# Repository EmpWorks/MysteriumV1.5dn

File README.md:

# MysteriumV1.5dn
Hotswap,  Underglow, Encoder ,Stepped_caps

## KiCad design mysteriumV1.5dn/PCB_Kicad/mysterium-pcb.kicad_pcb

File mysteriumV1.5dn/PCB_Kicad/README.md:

# MYSTERIUM V1.5dn
Originally created by coseyfannitutti 

**TKL keyboard assembled with only through hole components, including usb type-c**

### Disclaimer
This board is a heavily-modified coseyfannitutti MYSTERIUM Pcb While the schematic, basic layout etc is essentially the same, it supports additional features like Hot-swap,Encoder etc.

Key differences:
- supports hotswap PCB sockets
- added WS2812B Led strip footprint for backlit 
- Optional encoder support
- Oled support 

Disclaimer: Use these files at your own risk.

## Assembly
For the components required, you may refer to the bill of materials here [BOM](https://octopart.com/bom-tool/wr8C8imk).

Bottom plate for the [PCB](https://github.com/TheEmperor1510/MysteriumV1.5dn/tree/main/mysteriumV1.5dn/PCB_Kicad/bottom).

need 10k 804 smd Resistor for oled 
 
All the components can be soldered using a regular soldering iron.

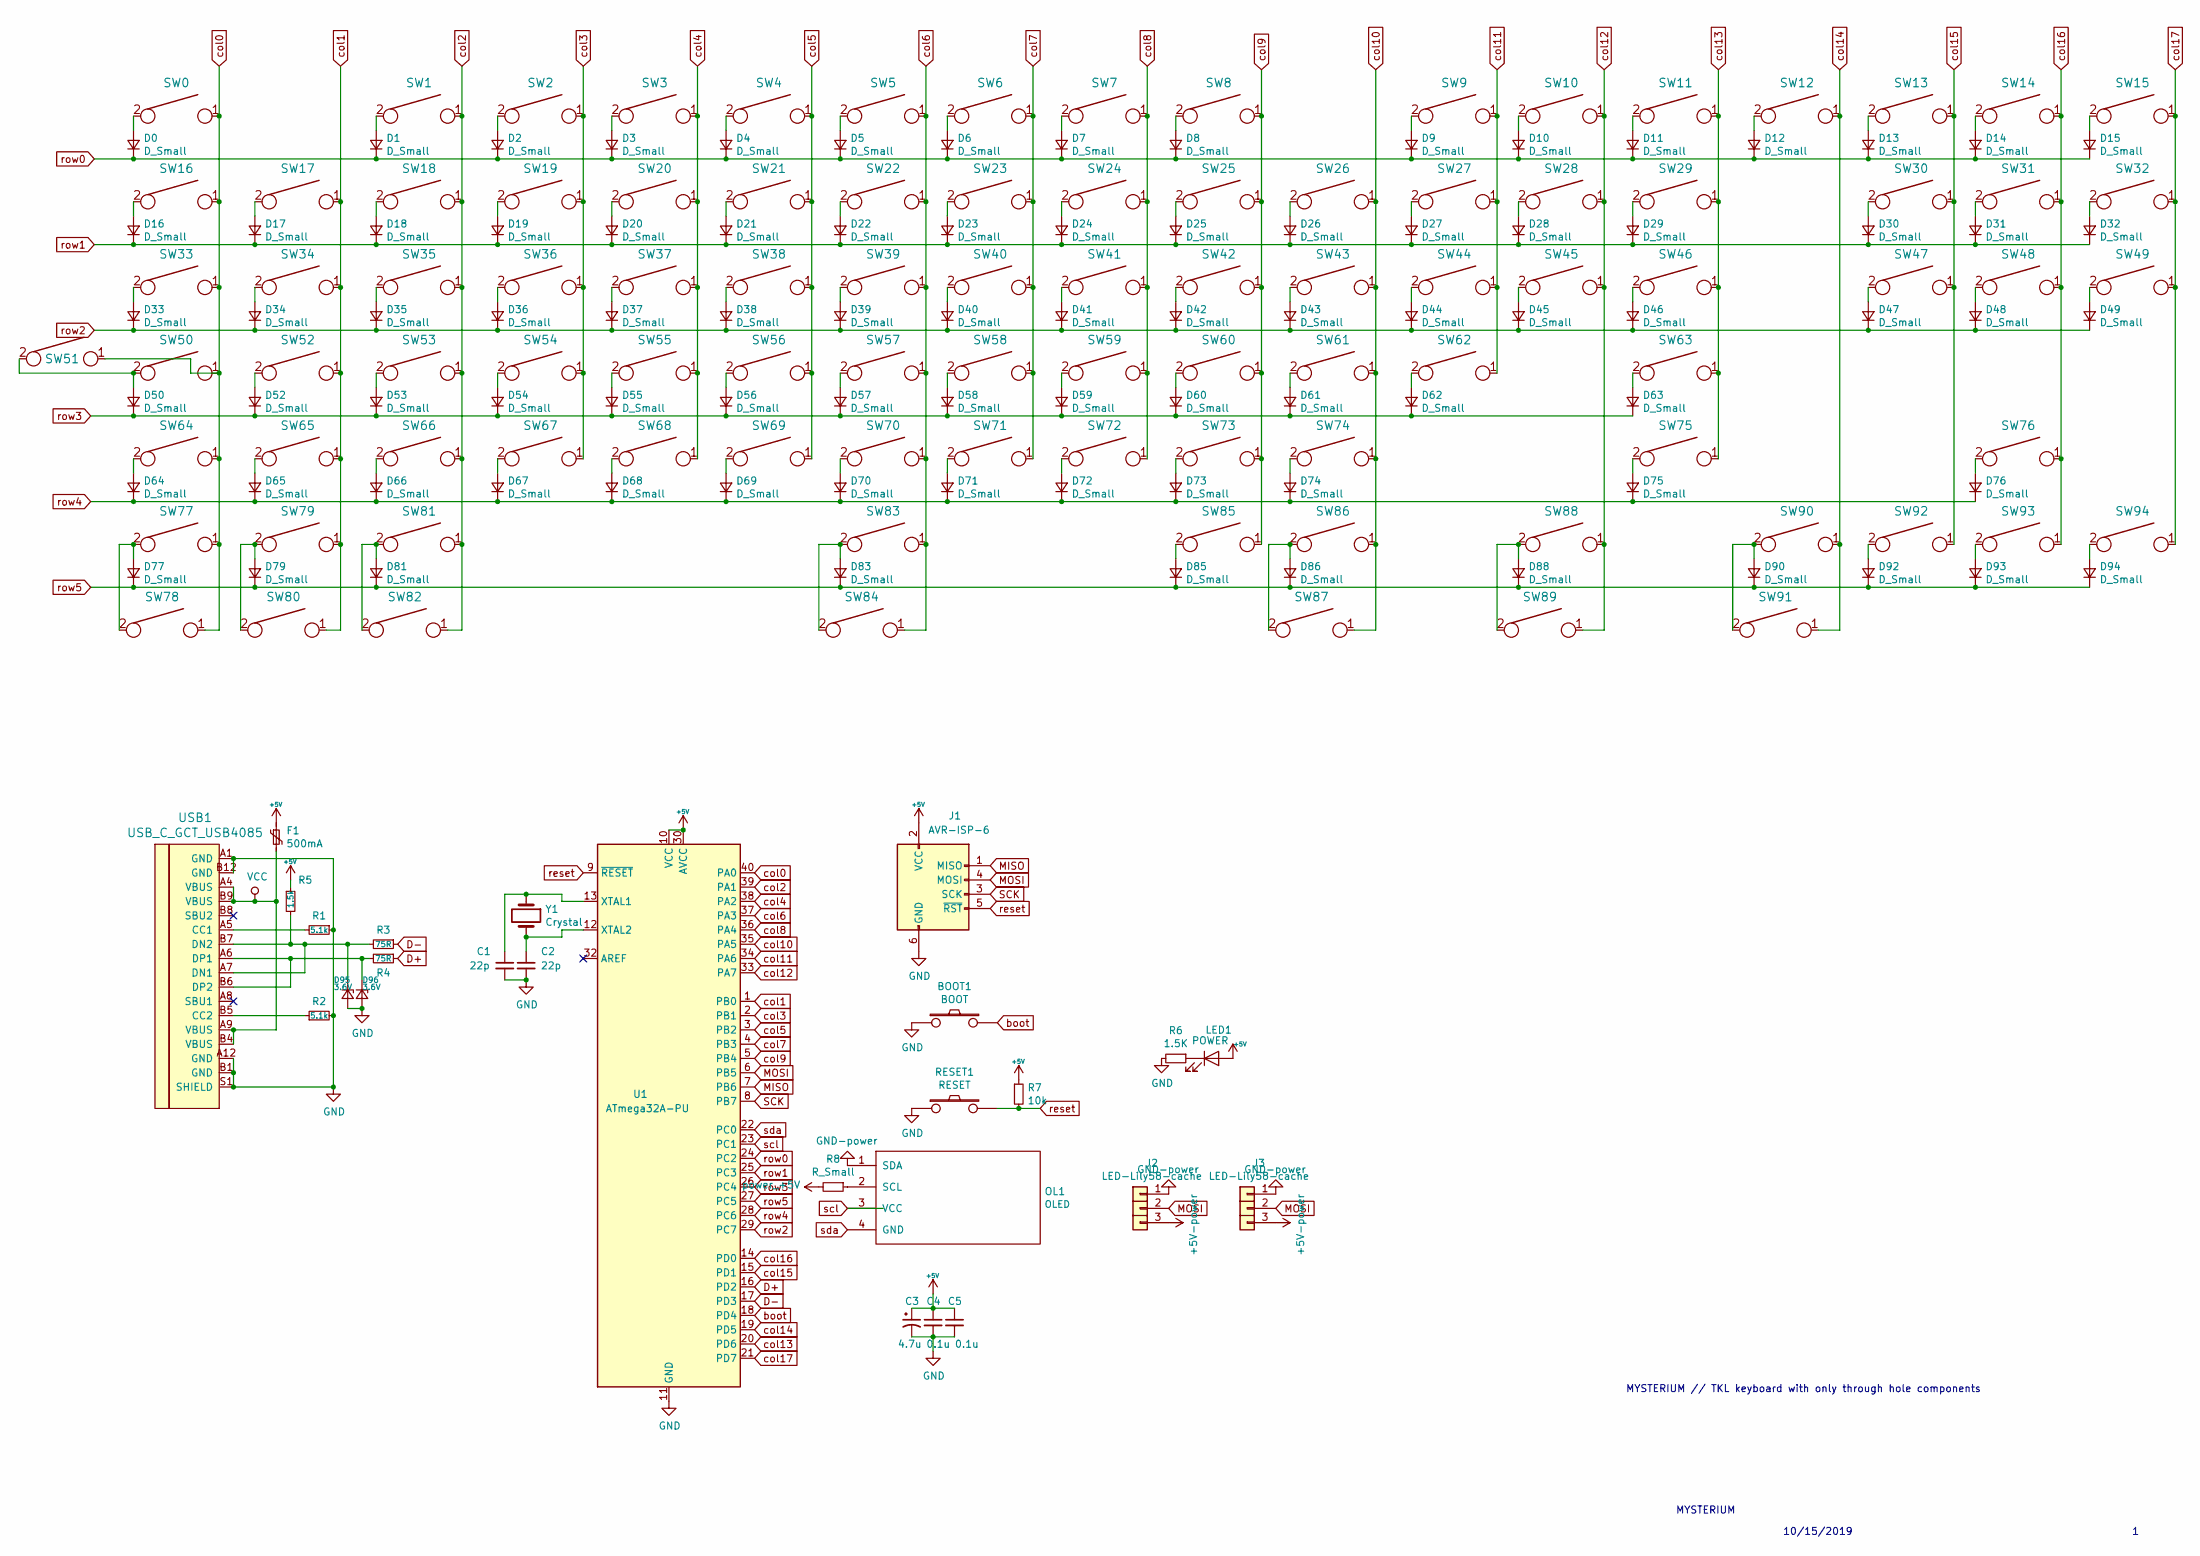
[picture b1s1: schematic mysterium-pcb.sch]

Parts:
BOOT1: BOOT; SW_PUSH_6mm
C1, C2: 22p; C_Disc_D3.0mm_W1.6mm_P2.50mm
C3: 4.7u; CP_Radial_D4.0mm_P1.50mm
C4, C5: 0.1u; C_Disc_D4.3mm_W1.9mm_P5.00mm
D0, D1, D2, D3, D4, D5, D6, D7, D8, D9, D10, D11, D12, D13, D14, D15, D16, D17, D18, D19, D20, D21, D22, D23, D24, D25, D26, D27, D28, D29, D30, D31, D32, D33, D34, D35, D36, D37, D38, D39, D40, D41, D42, D43, D44, D45, D46, D47, D48, D49, D50, D52, D53, D54, D55, D56, D57, D58, D59, D60, D61, D62, D63, D64, D65, D66, D67, D68, D69, D70, D71, D72, D73, D74, D75, D76, D77, D79, D81, D83, D85, D86, D88, D90, D92, D93, D94: D_Small; D_DO-35_SOD27_P5.08mm_Horizontal
D95, D96: 3.6V; D_DO-35_SOD27_P5.08mm_Horizontal
F1: 500mA; polyfuse_5.1mm
J1: AVR-ISP-6; AVR_ICSP_3x2
J2: LED-Lily58-cache; StripLED
J3: LED-Lily58-cache; FanPinHeader_1x03_P2.54mm_Vertical
LED1: POWER; LED_D3.0mm
OL1: OLED; PinHeader_1x04_P2.54mm_Vertical
R1, R2: 5.1k; R_Axial_DIN0204_L3.6mm_D1.6mm_P7.62mm_Horizontal
R3, R4: 75R; R_Axial_DIN0204_L3.6mm_D1.6mm_P7.62mm_Horizontal
R5: 1.5k; R_Axial_DIN0204_L3.6mm_D1.6mm_P7.62mm_Horizontal
R6: 1.5K; R_Axial_DIN0204_L3.6mm_D1.6mm_P7.62mm_Horizontal
R7: 10k; R_Axial_DIN0204_L3.6mm_D1.6mm_P7.62mm_Horizontal
R8: R_Small; R_0805_2012Metric_Pad1.20x1.40mm_HandSolder
RESET1: RESET; SW_PUSH_6mm
SW0, SW1, SW2, SW3, SW4, SW5, SW6, SW7, SW8, SW9, SW10, SW11, SW12, SW13, SW14, SW15, SW16, SW17, SW18, SW19, SW20, SW21, SW22, SW23, SW24, SW25, SW26, SW27, SW28, SW30, SW31, SW32, SW33, SW34, SW35, SW36, SW37, SW38, SW39, SW40, SW41, SW42, SW43, SW44, SW45, SW46, SW47, SW48, SW49, SW50, SW51, SW52, SW53, SW54, SW55, SW56, SW57, SW58, SW59, SW60, SW61, SW62, SW65, SW66, SW67, SW68, SW69, SW70, SW71, SW72, SW73, SW74, SW76, SW77, SW78, SW79, SW80, SW81, SW82, SW83, SW84, SW85, SW86, SW87, SW88, SW89, SW90, SW91, SW92, SW93, SW94: KEYSW; Kailh-PCB-Socket-1U-Cutout
SW29, SW63, SW64, SW75: KEYSW; Kailh-PCB-Socket-2U
U1: ATmega32A-PU; DIP-40_W15.24mm
USB1: USB_C_GCT_USB4085
Y1: Crystal; Crystal_HC49-4H_Vertical

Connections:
D+: R4.1, U1.16 (PD2)
D-: R3.1, U1.17 (PD3)
MISO: J1.1 (MISO), U1.7 (PB6)
MOSI: J1.4 (MOSI), J2.2, J3.2, U1.6 (PB5); also elsewhere on the board
unnamed: C1.1, U1.13 (XTAL1), Y1.1
unnamed: C2.1, U1.12 (XTAL2), Y1.2
unnamed: D0.2 (A), SW0.2
unnamed: D1.2 (A), SW1.2
unnamed: D2.2 (A), SW2.2
unnamed: D3.2 (A), SW3.2
unnamed: D4.2 (A), SW4.2
unnamed: D5.2 (A), SW5.2
unnamed: D6.2 (A), SW6.2
unnamed: D7.2 (A), SW7.2
unnamed: D8.2 (A), SW8.2
unnamed: D9.2 (A), SW9.2
unnamed: D10.2 (A), SW10.2
unnamed: D11.2 (A), SW11.2
unnamed: D12.2 (A), SW12.2
unnamed: D13.2 (A), SW13.2
unnamed: D14.2 (A), SW14.2
unnamed: D15.2 (A), SW15.2
unnamed: D16.2 (A), SW16.2
unnamed: D17.2 (A), SW17.2
unnamed: D18.2 (A), SW18.2
unnamed: D19.2 (A), SW19.2
unnamed: D20.2 (A), SW20.2
unnamed: D21.2 (A), SW21.2
unnamed: D22.2 (A), SW22.2
unnamed: D23.2 (A), SW23.2
unnamed: D24.2 (A), SW24.2
unnamed: D25.2 (A), SW25.2
unnamed: D26.2 (A), SW26.2
unnamed: D27.2 (A), SW27.2
unnamed: D28.2 (A), SW28.2
unnamed: D29.2 (A), SW29.2
unnamed: D30.2 (A), SW30.2
unnamed: D31.2 (A), SW31.2
unnamed: D32.2 (A), SW32.2
unnamed: D33.2 (A), SW33.2
unnamed: D34.2 (A), SW34.2
unnamed: D35.2 (A), SW35.2
unnamed: D36.2 (A), SW36.2
unnamed: D37.2 (A), SW37.2
unnamed: D38.2 (A), SW38.2
unnamed: D39.2 (A), SW39.2
unnamed: D40.2 (A), SW40.2
unnamed: D41.2 (A), SW41.2
unnamed: D42.2 (A), SW42.2
unnamed: D43.2 (A), SW43.2
unnamed: D44.2 (A), SW44.2
unnamed: D45.2 (A), SW45.2
unnamed: D46.2 (A), SW46.2
unnamed: D47.2 (A), SW47.2
unnamed: D48.2 (A), SW48.2
unnamed: D49.2 (A), SW49.2
unnamed: D50.2 (A), SW50.2, SW51.2
unnamed: D52.2 (A), SW52.2
unnamed: D53.2 (A), SW53.2
unnamed: D54.2 (A), SW54.2
unnamed: D55.2 (A), SW55.2
unnamed: D56.2 (A), SW56.2
unnamed: D57.2 (A), SW57.2
unnamed: D58.2 (A), SW58.2
unnamed: D59.2 (A), SW59.2
unnamed: D60.2 (A), SW60.2
unnamed: D61.2 (A), SW61.2
unnamed: D62.2 (A), SW62.2
unnamed: D63.2 (A), SW63.2
unnamed: D64.2 (A), SW64.2
unnamed: D65.2 (A), SW65.2
unnamed: D66.2 (A), SW66.2
unnamed: D67.2 (A), SW67.2
unnamed: D68.2 (A), SW68.2
unnamed: D69.2 (A), SW69.2
unnamed: D70.2 (A), SW70.2
unnamed: D71.2 (A), SW71.2
unnamed: D72.2 (A), SW72.2
unnamed: D73.2 (A), SW73.2
unnamed: D74.2 (A), SW74.2
unnamed: D75.2 (A), SW75.2
unnamed: D76.2 (A), SW76.2
unnamed: D77.2 (A), SW77.2, SW78.2
unnamed: D79.2 (A), SW79.2, SW80.2
unnamed: D81.2 (A), SW81.2, SW82.2
unnamed: D83.2 (A), SW83.2, SW84.2
unnamed: D85.2 (A), SW85.2
unnamed: D86.2 (A), SW86.2, SW87.2
unnamed: D88.2 (A), SW88.2, SW89.2
unnamed: D90.2 (A), SW90.2, SW91.2
unnamed: D92.2 (A), SW92.2
unnamed: D93.2 (A), SW93.2
unnamed: D94.2 (A), SW94.2
unnamed: D95.1 (K), R3.2, R5.2, USB1.A7 (DN1), USB1.B7 (DN2)
unnamed: D96.1 (K), R4.2, USB1.A6 (DP1), USB1.B6 (DP2)
unnamed: LED1.1 (K), R6.1
unnamed 96: OL1.2 (SCL), R8.1; also elsewhere on the board
unnamed: R1.2, USB1.A5 (CC1)
unnamed: R2.1, USB1.B5 (CC2)
SCK: J1.3 (SCK), U1.8 (PB7)
VCC: F1.2, USB1.A4 (VBUS), USB1.A9 (VBUS), USB1.B4 (VBUS), USB1.B9 (VBUS)
boot: BOOT1.2, U1.18 (PD4)
col0: SW0.1, SW16.1, SW33.1, SW50.1, SW51.1, SW64.1, SW77.1, SW78.1, U1.40 (PA0)
col1: SW17.1, SW34.1, SW52.1, SW65.1, SW79.1, SW80.1, U1.1 (PB0)
col2: SW1.1, SW18.1, SW35.1, SW53.1, SW66.1, SW81.1, SW82.1, U1.39 (PA1)
col3: SW2.1, SW19.1, SW36.1, SW54.1, SW67.1, U1.2 (PB1)
col4: SW3.1, SW20.1, SW37.1, SW55.1, SW68.1, U1.38 (PA2)
col5: SW4.1, SW21.1, SW38.1, SW56.1, SW69.1, U1.3 (PB2)
col6: SW5.1, SW22.1, SW39.1, SW57.1, SW70.1, SW83.1, SW84.1, U1.37 (PA3)
col7: SW6.1, SW23.1, SW40.1, SW58.1, SW71.1, U1.4 (PB3)
col8: SW7.1, SW24.1, SW41.1, SW59.1, SW72.1, U1.36 (PA4)
col9: SW8.1, SW25.1, SW42.1, SW60.1, SW73.1, SW85.1, U1.5 (PB4)
col10: SW26.1, SW43.1, SW61.1, SW74.1, SW86.1, SW87.1, U1.35 (PA5)
col11: SW9.1, SW27.1, SW44.1, SW62.1, U1.34 (PA6)
col12: SW10.1, SW28.1, SW45.1, SW88.1, SW89.1, U1.33 (PA7)
col13: SW11.1, SW29.1, SW46.1, SW63.1, SW75.1, U1.20 (PD6)
col14: SW12.1, SW90.1, SW91.1, U1.19 (PD5)
col15: SW13.1, SW30.1, SW47.1, SW92.1, U1.15 (PD1)
col16: SW14.1, SW31.1, SW48.1, SW76.1, SW93.1, U1.14 (PD0)
col17: SW15.1, SW32.1, SW49.1, SW94.1, U1.21 (PD7)
reset: J1.5 (~RST), R7.2, RESET1.2, U1.9 (~RESET)
row0: D0.1 (K), D1.1 (K), D2.1 (K), D3.1 (K), D4.1 (K), D5.1 (K), D6.1 (K), D7.1 (K), D8.1 (K), D9.1 (K), D10.1 (K), D11.1 (K), D12.1 (K), D13.1 (K), D14.1 (K), D15.1 (K), U1.24 (PC2)
row1: D16.1 (K), D17.1 (K), D18.1 (K), D19.1 (K), D20.1 (K), D21.1 (K), D22.1 (K), D23.1 (K), D24.1 (K), D25.1 (K), D26.1 (K), D27.1 (K), D28.1 (K), D29.1 (K), D30.1 (K), D31.1 (K), D32.1 (K), U1.25 (PC3)
row2: D33.1 (K), D34.1 (K), D35.1 (K), D36.1 (K), D37.1 (K), D38.1 (K), D39.1 (K), D40.1 (K), D41.1 (K), D42.1 (K), D43.1 (K), D44.1 (K), D45.1 (K), D46.1 (K), D47.1 (K), D48.1 (K), D49.1 (K), U1.29 (PC7)
row3: D50.1 (K), D52.1 (K), D53.1 (K), D54.1 (K), D55.1 (K), D56.1 (K), D57.1 (K), D58.1 (K), D59.1 (K), D60.1 (K), D61.1 (K), D62.1 (K), D63.1 (K), U1.26 (PC4)
row4: D64.1 (K), D65.1 (K), D66.1 (K), D67.1 (K), D68.1 (K), D69.1 (K), D70.1 (K), D71.1 (K), D72.1 (K), D73.1 (K), D74.1 (K), D75.1 (K), D76.1 (K), U1.28 (PC6)
row5: D77.1 (K), D79.1 (K), D81.1 (K), D83.1 (K), D85.1 (K), D86.1 (K), D88.1 (K), D90.1 (K), D92.1 (K), D93.1 (K), D94.1 (K), U1.27 (PC5)
scl: OL1.3 (VCC), U1.23 (PC1)
sda: OL1.4 (GND), U1.22 (PC0)

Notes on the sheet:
MYSTERIUM // TKL keyboard with only through hole components
10/15/2019
MYSTERIUM

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
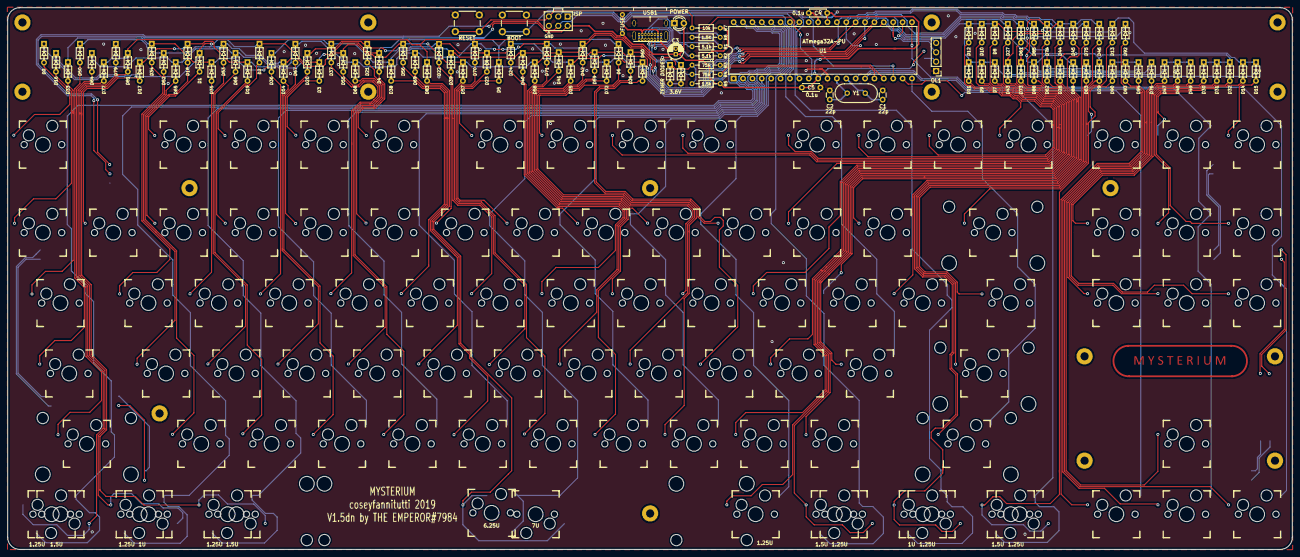
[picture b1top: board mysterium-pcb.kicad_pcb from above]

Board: 2 copper layers, 347.7 x 146.6 mm, 219 parts (1 on the bottom side), 131 nets.

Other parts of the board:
J2#2, J2#3, J2#4, J2#5, J2#6, J2#7, J2#8, J2#9, J2#10, J2#11, J2#12: LED-Lily58-cache; StripLED
R10k: R_Small; R_0805_2012Metric_Pad1.20x1.40mm_HandSolder
ST83: 6.25U; MX-6.25U-Stabilizer
ST84: 7U; MX-7U-Stabilizer

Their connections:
MOSI: J2#2.2, J2#3.2, J2#4.2, J2#5.2, J2#6.2, J2#7.2, J2#8.2, J2#9.2, J2#10.2, J2#11.2, J2#12.2; also elsewhere on the board
unnamed 96: R10k.1; also elsewhere on the board

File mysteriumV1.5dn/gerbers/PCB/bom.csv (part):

Designator,Footprint,Quantity,Value,LCSC Part #
ST83,MX-6.25U-Stabilizer,1,6.25U,
SW17,Kailh-PCB-Socket-1U-Cutout,1,KEYSW,
SW41,Kailh-PCB-Socket-1U-Cutout,1,KEYSW,
ST84,MX-7U-Stabilizer,1,7U,
C3,CP_Radial_D4.0mm_P1.50mm,1,4.7u,
LED1,LED_D3.0mm,1,POWER,
D28,D_DO-35_SOD27_P5.08mm_Horizontal,1,D_Small,
D36,D_DO-35_SOD27_P5.08mm_Horizontal,1,D_Small,
D11,D_DO-35_SOD27_P5.08mm_Horizontal,1,D_Small,
D14,D_DO-35_SOD27_P5.08mm_Horizontal,1,D_Small,
D90,D_DO-35_SOD27_P5.08mm_Horizontal,1,D_Small,
D92,D_DO-35_SOD27_P5.08mm_Horizontal,1,D_Small,
U1,DIP-40_W15.24mm,1,ATmega32A-PU,
BOOT1,SW_PUSH_6mm,1,BOOT,
C1,C_Disc_D3.0mm_W1.6mm_P2.50mm,1,22p,
C2,C_Disc_D3.0mm_W1.6mm_P2.50mm,1,22p,
C4,C_Disc_D4.3mm_W1.9mm_P5.00mm,1,0.1u,
C5,C_Disc_D4.3mm_W1.9mm_P5.00mm,1,0.1u,
D0,D_DO-35_SOD27_P5.08mm_Horizontal,1,D_Small,
D1,D_DO-35_SOD27_P5.08mm_Horizontal,1,D_Small,
D2,D_DO-35_SOD27_P5.08mm_Horizontal,1,D_Small,
D3,D_DO-35_SOD27_P5.08mm_Horizontal,1,D_Small,
D4,D_DO-35_SOD27_P5.08mm_Horizontal,1,D_Small,
D5,D_DO-35_SOD27_P5.08mm_Horizontal,1,D_Small,
D6,D_DO-35_SOD27_P5.08mm_Horizontal,1,D_Small,
D7,D_DO-35_SOD27_P5.08mm_Horizontal,1,D_Small,
D8,D_DO-35_SOD27_P5.08mm_Horizontal,1,D_Small,
D9,D_DO-35_SOD27_P5.08mm_Horizontal,1,D_Small,
D10,D_DO-35_SOD27_P5.08mm_Horizontal,1,D_Small,
D12,D_DO-35_SOD27_P5.08mm_Horizontal,1,D_Small,
D13,D_DO-35_SOD27_P5.08mm_Horizontal,1,D_Small,
D15,D_DO-35_SOD27_P5.08mm_Horizontal,1,D_Small,
D16,D_DO-35_SOD27_P5.08mm_Horizontal,1,D_Small,
D17,D_DO-35_SOD27_P5.08mm_Horizontal,1,D_Small,
D18,D_DO-35_SOD27_P5.08mm_Horizontal,1,D_Small,
D19,D_DO-35_SOD27_P5.08mm_Horizontal,1,D_Small,
D20,D_DO-35_SOD27_P5.08mm_Horizontal,1,D_Small,
D21,D_DO-35_SOD27_P5.08mm_Horizontal,1,D_Small,
D22,D_DO-35_SOD27_P5.08mm_Horizontal,1,D_Small,
D23,D_DO-35_SOD27_P5.08mm_Horizontal,1,D_Small,
D24,D_DO-35_SOD27_P5.08mm_Horizontal,1,D_Small,
D25,D_DO-35_SOD27_P5.08mm_Horizontal,1,D_Small,
D26,D_DO-35_SOD27_P5.08mm_Horizontal,1,D_Small,
D27,D_DO-35_SOD27_P5.08mm_Horizontal,1,D_Small,
D29,D_DO-35_SOD27_P5.08mm_Horizontal,1,D_Small,
D30,D_DO-35_SOD27_P5.08mm_Horizontal,1,D_Small,
D31,D_DO-35_SOD27_P5.08mm_Horizontal,1,D_Small,
D32,D_DO-35_SOD27_P5.08mm_Horizontal,1,D_Small,
D33,D_DO-35_SOD27_P5.08mm_Horizontal,1,D_Small,
D34,D_DO-35_SOD27_P5.08mm_Horizontal,1,D_Small,
D35,D_DO-35_SOD27_P5.08mm_Horizontal,1,D_Small,
D37,D_DO-35_SOD27_P5.08mm_Horizontal,1,D_Small,
D38,D_DO-35_SOD27_P5.08mm_Horizontal,1,D_Small,
D39,D_DO-35_SOD27_P5.08mm_Horizontal,1,D_Small,
D40,D_DO-35_SOD27_P5.08mm_Horizontal,1,D_Small,
D41,D_DO-35_SOD27_P5.08mm_Horizontal,1,D_Small,
D42,D_DO-35_SOD27_P5.08mm_Horizontal,1,D_Small,
D43,D_DO-35_SOD27_P5.08mm_Horizontal,1,D_Small,
D44,D_DO-35_SOD27_P5.08mm_Horizontal,1,D_Small,
D45,D_DO-35_SOD27_P5.08mm_Horizontal,1,D_Small,
D46,D_DO-35_SOD27_P5.08mm_Horizontal,1,D_Small,
D47,D_DO-35_SOD27_P5.08mm_Horizontal,1,D_Small,
D48,D_DO-35_SOD27_P5.08mm_Horizontal,1,D_Small,
D49,D_DO-35_SOD27_P5.08mm_Horizontal,1,D_Small,
D50,D_DO-35_SOD27_P5.08mm_Horizontal,1,D_Small,
D52,D_DO-35_SOD27_P5.08mm_Horizontal,1,D_Small,
D53,D_DO-35_SOD27_P5.08mm_Horizontal,1,D_Small,
D54,D_DO-35_SOD27_P5.08mm_Horizontal,1,D_Small,
D55,D_DO-35_SOD27_P5.08mm_Horizontal,1,D_Small,
D56,D_DO-35_SOD27_P5.08mm_Horizontal,1,D_Small,
D57,D_DO-35_SOD27_P5.08mm_Horizontal,1,D_Small,
D58,D_DO-35_SOD27_P5.08mm_Horizontal,1,D_Small,
D59,D_DO-35_SOD27_P5.08mm_Horizontal,1,D_Small,
D60,D_DO-35_SOD27_P5.08mm_Horizontal,1,D_Small,
D61,D_DO-35_SOD27_P5.08mm_Horizontal,1,D_Small,
D62,D_DO-35_SOD27_P5.08mm_Horizontal,1,D_Small,
D63,D_DO-35_SOD27_P5.08mm_Horizontal,1,D_Small,
D64,D_DO-35_SOD27_P5.08mm_Horizontal,1,D_Small,
D65,D_DO-35_SOD27_P5.08mm_Horizontal,1,D_Small,
D66,D_DO-35_SOD27_P5.08mm_Horizontal,1,D_Small,
D67,D_DO-35_SOD27_P5.08mm_Horizontal,1,D_Small,
D68,D_DO-35_SOD27_P5.08mm_Horizontal,1,D_Small,
D69,D_DO-35_SOD27_P5.08mm_Horizontal,1,D_Small,
D70,D_DO-35_SOD27_P5.08mm_Horizontal,1,D_Small,
D71,D_DO-35_SOD27_P5.08mm_Horizontal,1,D_Small,
D72,D_DO-35_SOD27_P5.08mm_Horizontal,1,D_Small,
D73,D_DO-35_SOD27_P5.08mm_Horizontal,1,D_Small,
D74,D_DO-35_SOD27_P5.08mm_Horizontal,1,D_Small,
D75,D_DO-35_SOD27_P5.08mm_Horizontal,1,D_Small,
D76,D_DO-35_SOD27_P5.08mm_Horizontal,1,D_Small,
D77,D_DO-35_SOD27_P5.08mm_Horizontal,1,D_Small,
D79,D_DO-35_SOD27_P5.08mm_Horizontal,1,D_Small,
D81,D_DO-35_SOD27_P5.08mm_Horizontal,1,D_Small,
D83,D_DO-35_SOD27_P5.08mm_Horizontal,1,D_Small,
D85,D_DO-35_SOD27_P5.08mm_Horizontal,1,D_Small,
D86,D_DO-35_SOD27_P5.08mm_Horizontal,1,D_Small,
D88,D_DO-35_SOD27_P5.08mm_Horizontal,1,D_Small,
D93,D_DO-35_SOD27_P5.08mm_Horizontal,1,D_Small,
D94,D_DO-35_SOD27_P5.08mm_Horizontal,1,D_Small,
D95,D_DO-35_SOD27_P5.08mm_Horizontal,1,3.6V,
D96,D_DO-35_SOD27_P5.08mm_Horizontal,1,3.6V,
F1,polyfuse_5.1mm,1,500mA,
J1,AVR_ICSP_3x2,1,AVR-ISP-6,
R1,R_Axial_DIN0204_L3.6mm_D1.6mm_P7.62mm_Horizontal,1,5.1k,
R2,R_Axial_DIN0204_L3.6mm_D1.6mm_P7.62mm_Horizontal,1,5.1k,
R3,R_Axial_DIN0204_L3.6mm_D1.6mm_P7.62mm_Horizontal,1,75R,
R4,R_Axial_DIN0204_L3.6mm_D1.6mm_P7.62mm_Horizontal,1,75R,
R5,R_Axial_DIN0204_L3.6mm_D1.6mm_P7.62mm_Horizontal,1,1.5k,
R6,R_Axial_DIN0204_L3.6mm_D1.6mm_P7.62mm_Horizontal,1,1.5K,
R7,R_Axial_DIN0204_L3.6mm_D1.6mm_P7.62mm_Horizontal,1,10k,
RESET1,SW_PUSH_6mm,1,RESET,
SW0,Kailh-PCB-Socket-1U-Cutout,1,KEYSW,
SW1,Kailh-PCB-Socket-1U-Cutout,1,KEYSW,
SW2,Kailh-PCB-Socket-1U-Cutout,1,KEYSW,
SW3,Kailh-PCB-Socket-1U-Cutout,1,KEYSW,
SW4,Kailh-PCB-Socket-1U-Cutout,1,KEYSW,
SW5,Kailh-PCB-Socket-1U-Cutout,1,KEYSW,
SW6,Kailh-PCB-Socket-1U-Cutout,1,KEYSW,
SW7,Kailh-PCB-Socket-1U-Cutout,1,KEYSW,
SW8,Kailh-PCB-Socket-1U-Cutout,1,KEYSW,
SW9,Kailh-PCB-Socket-1U-Cutout,1,KEYSW,
SW10,Kailh-PCB-Socket-1U-Cutout,1,KEYSW,
SW11,Kailh-PCB-Socket-1U-Cutout,1,KEYSW,
SW12,Kailh-PCB-Socket-1U-Cutout,1,KEYSW,
SW13,Kailh-PCB-Socket-1U-Cutout,1,KEYSW,
SW14,Kailh-PCB-Socket-1U-Cutout,1,KEYSW,
SW15,Kailh-PCB-Socket-1U-Cutout,1,KEYSW,
SW16,Kailh-PCB-Socket-1U-Cutout,1,KEYSW,
SW18,Kailh-PCB-Socket-1U-Cutout,1,KEYSW,
SW19,Kailh-PCB-Socket-1U-Cutout,1,KEYSW,
SW20,Kailh-PCB-Socket-1U-Cutout,1,KEYSW,
SW21,Kailh-PCB-Socket-1U-Cutout,1,KEYSW,
SW22,Kailh-PCB-Socket-1U-Cutout,1,KEYSW,
SW23,Kailh-PCB-Socket-1U-Cutout,1,KEYSW,
SW24,Kailh-PCB-Socket-1U-Cutout,1,KEYSW,
SW25,Kailh-PCB-Socket-1U-Cutout,1,KEYSW,
SW26,Kailh-PCB-Socket-1U-Cutout,1,KEYSW,
SW27,Kailh-PCB-Socket-1U-Cutout,1,KEYSW,
SW28,Kailh-PCB-Socket-1U-Cutout,1,KEYSW,
SW29,Kailh-PCB-Socket-2U,1,KEYSW,
SW30,Kailh-PCB-Socket-1U-Cutout,1,KEYSW,
SW31,Kailh-PCB-Socket-1U-Cutout,1,KEYSW,
SW32,Kailh-PCB-Socket-1U-Cutout,1,KEYSW,
SW33,Kailh-PCB-Socket-1U-Cutout,1,KEYSW,
SW34,Kailh-PCB-Socket-1U-Cutout,1,KEYSW,
SW35,Kailh-PCB-Socket-1U-Cutout,1,KEYSW,
SW36,Kailh-PCB-Socket-1U-Cutout,1,KEYSW,
SW37,Kailh-PCB-Socket-1U-Cutout,1,KEYSW,
SW38,Kailh-PCB-Socket-1U-Cutout,1,KEYSW,
SW39,Kailh-PCB-Socket-1U-Cutout,1,KEYSW,
SW40,Kailh-PCB-Socket-1U-Cutout,1,KEYSW,
SW42,Kailh-PCB-Socket-1U-Cutout,1,KEYSW,
SW43,Kailh-PCB-Socket-1U-Cutout,1,KEYSW,
SW44,Kailh-PCB-Socket-1U-Cutout,1,KEYSW,
SW45,Kailh-PCB-Socket-1U-Cutout,1,KEYSW,
SW46,Kailh-PCB-Socket-1U-Cutout,1,KEYSW,
SW47,Kailh-PCB-Socket-1U-Cutout,1,KEYSW,
SW48,Kailh-PCB-Socket-1U-Cutout,1,KEYSW,
SW49,Kailh-PCB-Socket-1U-Cutout,1,KEYSW,
SW50,Kailh-PCB-Socket-1U-Cutout,1,KEYSW,
SW52,Kailh-PCB-Socket-1U-Cutout,1,KEYSW,
SW53,Kailh-PCB-Socket-1U-Cutout,1,KEYSW,
SW54,Kailh-PCB-Socket-1U-Cutout,1,KEYSW,
SW55,Kailh-PCB-Socket-1U-Cutout,1,KEYSW,
SW56,Kailh-PCB-Socket-1U-Cutout,1,KEYSW,
SW57,Kailh-PCB-Socket-1U-Cutout,1,KEYSW,
SW58,Kailh-PCB-Socket-1U-Cutout,1,KEYSW,
SW59,Kailh-PCB-Socket-1U-Cutout,1,KEYSW,
SW60,Kailh-PCB-Socket-1U-Cutout,1,KEYSW,
SW61,Kailh-PCB-Socket-1U-Cutout,1,KEYSW,
SW62,Kailh-PCB-Socket-1U-Cutout,1,KEYSW,
SW63,Kailh-PCB-Socket-2U,1,KEYSW,
SW64,Kailh-PCB-Socket-2U,1,KEYSW,
SW65,Kailh-PCB-Socket-1U-Cutout,1,KEYSW,
SW66,Kailh-PCB-Socket-1U-Cutout,1,KEYSW,
SW67,Kailh-PCB-Socket-1U-Cutout,1,KEYSW,
SW68,Kailh-PCB-Socket-1U-Cutout,1,KEYSW,
SW69,Kailh-PCB-Socket-1U-Cutout,1,KEYSW,
SW70,Kailh-PCB-Socket-1U-Cutout,1,KEYSW,
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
